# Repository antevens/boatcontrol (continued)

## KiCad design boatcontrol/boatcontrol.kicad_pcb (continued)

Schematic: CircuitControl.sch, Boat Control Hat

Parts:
D4101: 20mA R/G CC; LED_D5.0mm-3
SW4101, SW4102: ESB30; SW_PUSH_ESB30_DPDT

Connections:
+12P: SW4101.6 (C), SW4102.6 (C); also elsewhere on the board
/Add-On Relay Board 1/MixedBlock1/MixedControl1/DIG_OFF: SW4101.4 (A); also elsewhere on the board
/Add-On Relay Board 1/MixedBlock1/MixedControl1/DIG_ON: SW4102.4 (A); also elsewhere on the board
/Add-On Relay Board 1/MixedBlock1/MixedControl1/DISABLED_INDICATOR: SW4101.3 (C), SW4102.3 (C)
/Add-On Relay Board 1/MixedBlock1/MixedControl1/OFF_LED: D4101.3 (A2); also elsewhere on the board
/Add-On Relay Board 1/MixedBlock1/MixedControl1/OFF_TO_ON: SW4101.1 (A), SW4102.5 (B)
/Add-On Relay Board 1/MixedBlock1/MixedControl1/ON_LED: D4101.1 (A1); also elsewhere on the board
/Add-On Relay Board 1/MixedBlock1/MixedControl1/ON_TO_OFF: SW4101.5 (B), SW4102.1 (A)
/Add-On Relay Board 1/MixedBlock1/OFF_SIGNAL_1: SW4101.2 (B); also elsewhere on the board
/Add-On Relay Board 1/MixedBlock1/ON_SIGNAL_1: SW4102.2 (B); also elsewhere on the board
GND: D4101.2 (K); also elsewhere on the board

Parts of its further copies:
D4201, D4301, D4401, D4601, D4701, D4801, D4901, D8901, D9001, D9101, D9201, D9401, D9501, D9601, D9701: 20mA R/G CC; LED_D5.0mm-3
SW4201, SW4202, SW4301, SW4302, SW4401, SW4402, SW4601, SW4602, SW4701, SW4702, SW4801, SW4802, SW4901, SW4902, SW8901, SW8902, SW9001, SW9002, SW9101, SW9102, SW9201, SW9202, SW9401, SW9402, SW9501, SW9502, SW9601, SW9602, SW9701, SW9702: ESB30; SW_PUSH_ESB30_DPDT

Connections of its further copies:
+12P: SW4201.6 (C), SW4202.6 (C), SW4301.6 (C), SW4302.6 (C), SW4401.6 (C), SW4402.6 (C), SW4601.6 (C), SW4602.6 (C), SW4701.6 (C), SW4702.6 (C), SW4801.6 (C), SW4802.6 (C), SW4901.6 (C), SW4902.6 (C), SW8901.6 (C), SW8902.6 (C), SW9001.6 (C), SW9002.6 (C), SW9101.6 (C), SW9102.6 (C), SW9201.6 (C), SW9202.6 (C), SW9401.6 (C), SW9402.6 (C), SW9501.6 (C), SW9502.6 (C), SW9601.6 (C), SW9602.6 (C), SW9701.6 (C), SW9702.6 (C); also elsewhere on the board
/Add-On Relay Board 1/MixedBlock1/MixedControl2/DIG_OFF: SW4401.4 (A); also elsewhere on the board
/Add-On Relay Board 1/MixedBlock1/MixedControl2/DIG_ON: SW4402.4 (A); also elsewhere on the board
/Add-On Relay Board 1/MixedBlock1/MixedControl2/DISABLED_INDICATOR: SW4401.3 (C), SW4402.3 (C)
/Add-On Relay Board 1/MixedBlock1/MixedControl2/OFF_LED: D4401.3 (A2); also elsewhere on the board
/Add-On Relay Board 1/MixedBlock1/MixedControl2/OFF_TO_ON: SW4401.1 (A), SW4402.5 (B)
/Add-On Relay Board 1/MixedBlock1/MixedControl2/ON_LED: D4401.1 (A1); also elsewhere on the board
/Add-On Relay Board 1/MixedBlock1/MixedControl2/ON_TO_OFF: SW4401.5 (B), SW4402.1 (A)
/Add-On Relay Board 1/MixedBlock1/MixedControl3/DIG_OFF: SW4201.4 (A); also elsewhere on the board
/Add-On Relay Board 1/MixedBlock1/MixedControl3/DIG_ON: SW4202.4 (A); also elsewhere on the board
/Add-On Relay Board 1/MixedBlock1/MixedControl3/DISABLED_INDICATOR: SW4201.3 (C), SW4202.3 (C)
/Add-On Relay Board 1/MixedBlock1/MixedControl3/OFF_LED: D4201.3 (A2); also elsewhere on the board
/Add-On Relay Board 1/MixedBlock1/MixedControl3/OFF_TO_ON: SW4201.1 (A), SW4202.5 (B)
/Add-On Relay Board 1/MixedBlock1/MixedControl3/ON_LED: D4201.1 (A1); also elsewhere on the board
/Add-On Relay Board 1/MixedBlock1/MixedControl3/ON_TO_OFF: SW4201.5 (B), SW4202.1 (A)
/Add-On Relay Board 1/MixedBlock1/MixedControl4/DIG_OFF: SW4301.4 (A); also elsewhere on the board
/Add-On Relay Board 1/MixedBlock1/MixedControl4/DIG_ON: SW4302.4 (A); also elsewhere on the board
/Add-On Relay Board 1/MixedBlock1/MixedControl4/DISABLED_INDICATOR: SW4301.3 (C), SW4302.3 (C)
/Add-On Relay Board 1/MixedBlock1/MixedControl4/OFF_LED: D4301.3 (A2); also elsewhere on the board
/Add-On Relay Board 1/MixedBlock1/MixedControl4/OFF_TO_ON: SW4301.1 (A), SW4302.5 (B)
/Add-On Relay Board 1/MixedBlock1/MixedControl4/ON_LED: D4301.1 (A1); also elsewhere on the board
/Add-On Relay Board 1/MixedBlock1/MixedControl4/ON_TO_OFF: SW4301.5 (B), SW4302.1 (A)
/Add-On Relay Board 1/MixedBlock1/OFF_SIGNAL_2: SW4401.2 (B); also elsewhere on the board
/Add-On Relay Board 1/MixedBlock1/OFF_SIGNAL_3: SW4201.2 (B); also elsewhere on the board
/Add-On Relay Board 1/MixedBlock1/OFF_SIGNAL_4: SW4301.2 (B); also elsewhere on the board
/Add-On Relay Board 1/MixedBlock1/ON_SIGNAL_2: SW4402.2 (B); also elsewhere on the board
/Add-On Relay Board 1/MixedBlock1/ON_SIGNAL_3: SW4202.2 (B); also elsewhere on the board
/Add-On Relay Board 1/MixedBlock1/ON_SIGNAL_4: SW4302.2 (B); also elsewhere on the board
/Add-On Relay Board 1/MixedBlock2/MixedControl1/DIG_OFF: SW4601.4 (A); also elsewhere on the board
/Add-On Relay Board 1/MixedBlock2/MixedControl1/DIG_ON: SW4602.4 (A); also elsewhere on the board
/Add-On Relay Board 1/MixedBlock2/MixedControl1/DISABLED_INDICATOR: SW4601.3 (C), SW4602.3 (C)
/Add-On Relay Board 1/MixedBlock2/MixedControl1/OFF_LED: D4601.3 (A2); also elsewhere on the board
/Add-On Relay Board 1/MixedBlock2/MixedControl1/OFF_TO_ON: SW4601.1 (A), SW4602.5 (B)
/Add-On Relay Board 1/MixedBlock2/MixedControl1/ON_LED: D4601.1 (A1); also elsewhere on the board
/Add-On Relay Board 1/MixedBlock2/MixedControl1/ON_TO_OFF: SW4601.5 (B), SW4602.1 (A)
/Add-On Relay Board 1/MixedBlock2/MixedControl2/DIG_OFF: SW4901.4 (A); also elsewhere on the board
/Add-On Relay Board 1/MixedBlock2/MixedControl2/DIG_ON: SW4902.4 (A); also elsewhere on the board
/Add-On Relay Board 1/MixedBlock2/MixedControl2/DISABLED_INDICATOR: SW4901.3 (C), SW4902.3 (C)
/Add-On Relay Board 1/MixedBlock2/MixedControl2/OFF_LED: D4901.3 (A2); also elsewhere on the board
/Add-On Relay Board 1/MixedBlock2/MixedControl2/OFF_TO_ON: SW4901.1 (A), SW4902.5 (B)
/Add-On Relay Board 1/MixedBlock2/MixedControl2/ON_LED: D4901.1 (A1); also elsewhere on the board
/Add-On Relay Board 1/MixedBlock2/MixedControl2/ON_TO_OFF: SW4901.5 (B), SW4902.1 (A)
/Add-On Relay Board 1/MixedBlock2/MixedControl3/DIG_OFF: SW4701.4 (A); also elsewhere on the board
/Add-On Relay Board 1/MixedBlock2/MixedControl3/DIG_ON: SW4702.4 (A); also elsewhere on the board
/Add-On Relay Board 1/MixedBlock2/MixedControl3/DISABLED_INDICATOR: SW4701.3 (C), SW4702.3 (C)
/Add-On Relay Board 1/MixedBlock2/MixedControl3/OFF_LED: D4701.3 (A2); also elsewhere on the board
/Add-On Relay Board 1/MixedBlock2/MixedControl3/OFF_TO_ON: SW4701.1 (A), SW4702.5 (B)
/Add-On Relay Board 1/MixedBlock2/MixedControl3/ON_LED: D4701.1 (A1); also elsewhere on the board
/Add-On Relay Board 1/MixedBlock2/MixedControl3/ON_TO_OFF: SW4701.5 (B), SW4702.1 (A)
/Add-On Relay Board 1/MixedBlock2/MixedControl4/DIG_OFF: SW4801.4 (A); also elsewhere on the board
/Add-On Relay Board 1/MixedBlock2/MixedControl4/DIG_ON: SW4802.4 (A); also elsewhere on the board
/Add-On Relay Board 1/MixedBlock2/MixedControl4/DISABLED_INDICATOR: SW4801.3 (C), SW4802.3 (C)
/Add-On Relay Board 1/MixedBlock2/MixedControl4/OFF_LED: D4801.3 (A2); also elsewhere on the board
/Add-On Relay Board 1/MixedBlock2/MixedControl4/OFF_TO_ON: SW4801.1 (A), SW4802.5 (B)
/Add-On Relay Board 1/MixedBlock2/MixedControl4/ON_LED: D4801.1 (A1); also elsewhere on the board
/Add-On Relay Board 1/MixedBlock2/MixedControl4/ON_TO_OFF: SW4801.5 (B), SW4802.1 (A)
/Add-On Relay Board 1/MixedBlock2/OFF_SIGNAL_1: SW4601.2 (B); also elsewhere on the board
/Add-On Relay Board 1/MixedBlock2/OFF_SIGNAL_2: SW4901.2 (B); also elsewhere on the board
/Add-On Relay Board 1/MixedBlock2/OFF_SIGNAL_3: SW4701.2 (B); also elsewhere on the board
/Add-On Relay Board 1/MixedBlock2/OFF_SIGNAL_4: SW4801.2 (B); also elsewhere on the board
/Add-On Relay Board 1/MixedBlock2/ON_SIGNAL_1: SW4602.2 (B); also elsewhere on the board
/Add-On Relay Board 1/MixedBlock2/ON_SIGNAL_2: SW4902.2 (B); also elsewhere on the board
/Add-On Relay Board 1/MixedBlock2/ON_SIGNAL_3: SW4702.2 (B); also elsewhere on the board
/Add-On Relay Board 1/MixedBlock2/ON_SIGNAL_4: SW4802.2 (B); also elsewhere on the board
/Add-On Relay Board 2/MixedBlock1/MixedControl1/DIG_OFF: SW8902.4 (A); also elsewhere on the board
/Add-On Relay Board 2/MixedBlock1/MixedControl1/DIG_ON: SW8901.4 (A); also elsewhere on the board
/Add-On Relay Board 2/MixedBlock1/MixedControl1/DISABLED_INDICATOR: SW8901.3 (C), SW8902.3 (C)
/Add-On Relay Board 2/MixedBlock1/MixedControl1/OFF_LED: D8901.3 (A2); also elsewhere on the board
/Add-On Relay Board 2/MixedBlock1/MixedControl1/OFF_TO_ON: SW8901.5 (B), SW8902.1 (A)
/Add-On Relay Board 2/MixedBlock1/MixedControl1/ON_LED: D8901.1 (A1); also elsewhere on the board
/Add-On Relay Board 2/MixedBlock1/MixedControl1/ON_TO_OFF: SW8901.1 (A), SW8902.5 (B)
/Add-On Relay Board 2/MixedBlock1/MixedControl2/DIG_OFF: SW9202.4 (A); also elsewhere on the board
/Add-On Relay Board 2/MixedBlock1/MixedControl2/DIG_ON: SW9201.4 (A); also elsewhere on the board
/Add-On Relay Board 2/MixedBlock1/MixedControl2/DISABLED_INDICATOR: SW9201.3 (C), SW9202.3 (C)
/Add-On Relay Board 2/MixedBlock1/MixedControl2/OFF_LED: D9201.3 (A2); also elsewhere on the board
/Add-On Relay Board 2/MixedBlock1/MixedControl2/OFF_TO_ON: SW9201.5 (B), SW9202.1 (A)
/Add-On Relay Board 2/MixedBlock1/MixedControl2/ON_LED: D9201.1 (A1); also elsewhere on the board
/Add-On Relay Board 2/MixedBlock1/MixedControl2/ON_TO_OFF: SW9201.1 (A), SW9202.5 (B)
/Add-On Relay Board 2/MixedBlock1/MixedControl3/DIG_OFF: SW9002.4 (A); also elsewhere on the board
/Add-On Relay Board 2/MixedBlock1/MixedControl3/DIG_ON: SW9001.4 (A); also elsewhere on the board
/Add-On Relay Board 2/MixedBlock1/MixedControl3/DISABLED_INDICATOR: SW9001.3 (C), SW9002.3 (C)
/Add-On Relay Board 2/MixedBlock1/MixedControl3/OFF_LED: D9001.3 (A2); also elsewhere on the board
/Add-On Relay Board 2/MixedBlock1/MixedControl3/OFF_TO_ON: SW9001.5 (B), SW9002.1 (A)
/Add-On Relay Board 2/MixedBlock1/MixedControl3/ON_LED: D9001.1 (A1); also elsewhere on the board
/Add-On Relay Board 2/MixedBlock1/MixedControl3/ON_TO_OFF: SW9001.1 (A), SW9002.5 (B)
/Add-On Relay Board 2/MixedBlock1/MixedControl4/DIG_OFF: SW9102.4 (A); also elsewhere on the board
/Add-On Relay Board 2/MixedBlock1/MixedControl4/DIG_ON: SW9101.4 (A); also elsewhere on the board
/Add-On Relay Board 2/MixedBlock1/MixedControl4/DISABLED_INDICATOR: SW9101.3 (C), SW9102.3 (C)
/Add-On Relay Board 2/MixedBlock1/MixedControl4/OFF_LED: D9101.3 (A2); also elsewhere on the board
/Add-On Relay Board 2/MixedBlock1/MixedControl4/OFF_TO_ON: SW9101.5 (B), SW9102.1 (A)
/Add-On Relay Board 2/MixedBlock1/MixedControl4/ON_LED: D9101.1 (A1); also elsewhere on the board
/Add-On Relay Board 2/MixedBlock1/MixedControl4/ON_TO_OFF: SW9101.1 (A), SW9102.5 (B)
/Add-On Relay Board 2/MixedBlock1/OFF_SIGNAL_1: SW8902.2 (B); also elsewhere on the board
/Add-On Relay Board 2/MixedBlock1/OFF_SIGNAL_2: SW9202.2 (B); also elsewhere on the board
/Add-On Relay Board 2/MixedBlock1/OFF_SIGNAL_3: SW9002.2 (B); also elsewhere on the board
/Add-On Relay Board 2/MixedBlock1/OFF_SIGNAL_4: SW9102.2 (B); also elsewhere on the board
/Add-On Relay Board 2/MixedBlock1/ON_SIGNAL_1: SW8901.2 (B); also elsewhere on the board
/Add-On Relay Board 2/MixedBlock1/ON_SIGNAL_2: SW9201.2 (B); also elsewhere on the board
/Add-On Relay Board 2/MixedBlock1/ON_SIGNAL_3: SW9001.2 (B); also elsewhere on the board
/Add-On Relay Board 2/MixedBlock1/ON_SIGNAL_4: SW9101.2 (B); also elsewhere on the board
/Add-On Relay Board 2/MixedBlock2/MixedControl1/DIG_OFF: SW9402.4 (A); also elsewhere on the board
/Add-On Relay Board 2/MixedBlock2/MixedControl1/DIG_ON: SW9401.4 (A); also elsewhere on the board
/Add-On Relay Board 2/MixedBlock2/MixedControl1/DISABLED_INDICATOR: SW9401.3 (C), SW9402.3 (C)
/Add-On Relay Board 2/MixedBlock2/MixedControl1/OFF_LED: D9401.3 (A2); also elsewhere on the board
/Add-On Relay Board 2/MixedBlock2/MixedControl1/OFF_TO_ON: SW9401.5 (B), SW9402.1 (A)
/Add-On Relay Board 2/MixedBlock2/MixedControl1/ON_LED: D9401.1 (A1); also elsewhere on the board
/Add-On Relay Board 2/MixedBlock2/MixedControl1/ON_TO_OFF: SW9401.1 (A), SW9402.5 (B)
/Add-On Relay Board 2/MixedBlock2/MixedControl2/DIG_OFF: SW9702.4 (A); also elsewhere on the board
/Add-On Relay Board 2/MixedBlock2/MixedControl2/DIG_ON: SW9701.4 (A); also elsewhere on the board
/Add-On Relay Board 2/MixedBlock2/MixedControl2/DISABLED_INDICATOR: SW9701.3 (C), SW9702.3 (C)
/Add-On Relay Board 2/MixedBlock2/MixedControl2/OFF_LED: D9701.3 (A2); also elsewhere on the board
/Add-On Relay Board 2/MixedBlock2/MixedControl2/OFF_TO_ON: SW9701.5 (B), SW9702.1 (A)
/Add-On Relay Board 2/MixedBlock2/MixedControl2/ON_LED: D9701.1 (A1); also elsewhere on the board
/Add-On Relay Board 2/MixedBlock2/MixedControl2/ON_TO_OFF: SW9701.1 (A), SW9702.5 (B)
/Add-On Relay Board 2/MixedBlock2/MixedControl3/DIG_OFF: SW9502.4 (A); also elsewhere on the board
/Add-On Relay Board 2/MixedBlock2/MixedControl3/DIG_ON: SW9501.4 (A); also elsewhere on the board
/Add-On Relay Board 2/MixedBlock2/MixedControl3/DISABLED_INDICATOR: SW9501.3 (C), SW9502.3 (C)
/Add-On Relay Board 2/MixedBlock2/MixedControl3/OFF_LED: D9501.3 (A2); also elsewhere on the board
/Add-On Relay Board 2/MixedBlock2/MixedControl3/OFF_TO_ON: SW9501.5 (B), SW9502.1 (A)
/Add-On Relay Board 2/MixedBlock2/MixedControl3/ON_LED: D9501.1 (A1); also elsewhere on the board
/Add-On Relay Board 2/MixedBlock2/MixedControl3/ON_TO_OFF: SW9501.1 (A), SW9502.5 (B)
/Add-On Relay Board 2/MixedBlock2/MixedControl4/DIG_OFF: SW9602.4 (A); also elsewhere on the board
/Add-On Relay Board 2/MixedBlock2/MixedControl4/DIG_ON: SW9601.4 (A); also elsewhere on the board
/Add-On Relay Board 2/MixedBlock2/MixedControl4/DISABLED_INDICATOR: SW9601.3 (C), SW9602.3 (C)
/Add-On Relay Board 2/MixedBlock2/MixedControl4/OFF_LED: D9601.3 (A2); also elsewhere on the board
/Add-On Relay Board 2/MixedBlock2/MixedControl4/OFF_TO_ON: SW9601.5 (B), SW9602.1 (A)
/Add-On Relay Board 2/MixedBlock2/MixedControl4/ON_LED: D9601.1 (A1); also elsewhere on the board
/Add-On Relay Board 2/MixedBlock2/MixedControl4/ON_TO_OFF: SW9601.1 (A), SW9602.5 (B)
/Add-On Relay Board 2/MixedBlock2/OFF_SIGNAL_1: SW9402.2 (B); also elsewhere on the board
/Add-On Relay Board 2/MixedBlock2/OFF_SIGNAL_2: SW9702.2 (B); also elsewhere on the board
/Add-On Relay Board 2/MixedBlock2/OFF_SIGNAL_3: SW9502.2 (B); also elsewhere on the board
/Add-On Relay Board 2/MixedBlock2/OFF_SIGNAL_4: SW9602.2 (B); also elsewhere on the board
/Add-On Relay Board 2/MixedBlock2/ON_SIGNAL_1: SW9401.2 (B); also elsewhere on the board
/Add-On Relay Board 2/MixedBlock2/ON_SIGNAL_2: SW9701.2 (B); also elsewhere on the board
/Add-On Relay Board 2/MixedBlock2/ON_SIGNAL_3: SW9501.2 (B); also elsewhere on the board
/Add-On Relay Board 2/MixedBlock2/ON_SIGNAL_4: SW9601.2 (B); also elsewhere on the board
GND: D4201.2 (K), D4301.2 (K), D4401.2 (K), D4601.2 (K), D4701.2 (K), D4801.2 (K), D4901.2 (K), D8901.2 (K), D9001.2 (K), D9101.2 (K), D9201.2 (K), D9401.2 (K), D9501.2 (K), D9601.2 (K), D9701.2 (K); also elsewhere on the board

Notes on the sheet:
Buttons offer manual overide of relays using direct 12V. There is no timing/pulse circuit when operating the switches so care should be taken not to energise relay coils for more than a few seconds. Setting each coil to "on" will disable the opposing coil to prevent both coils from being energnized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

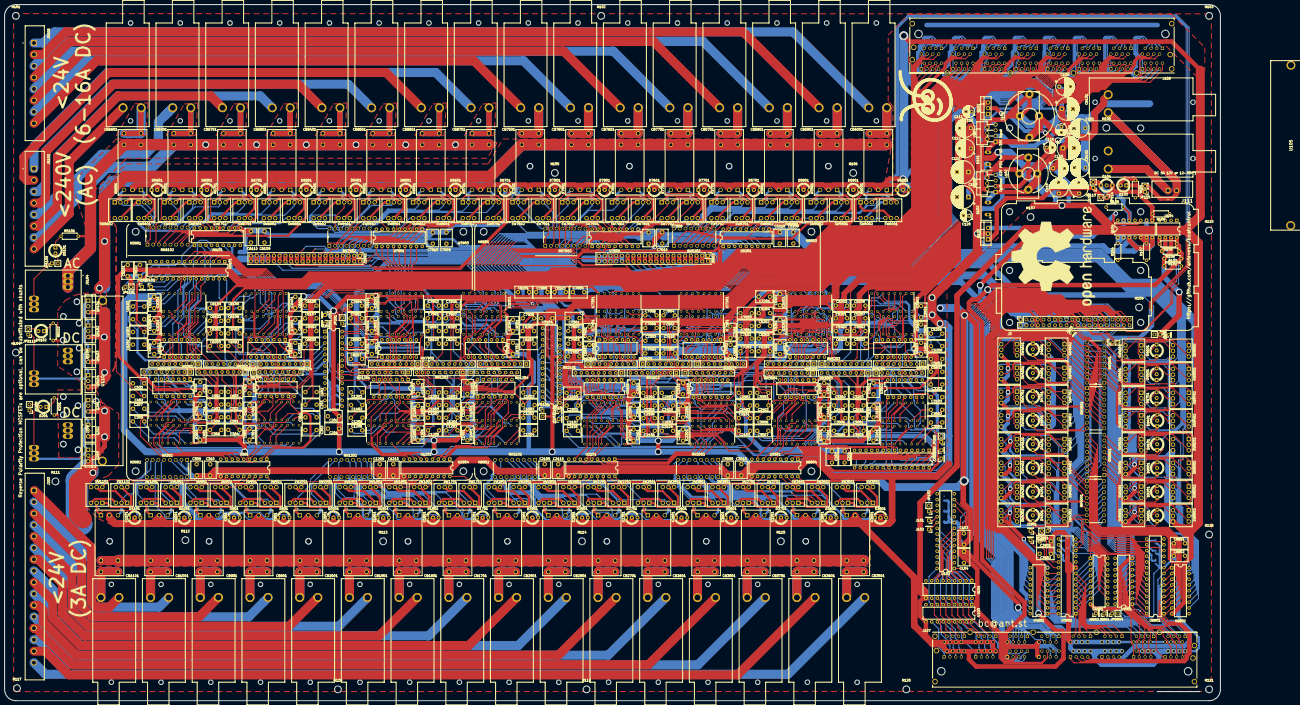
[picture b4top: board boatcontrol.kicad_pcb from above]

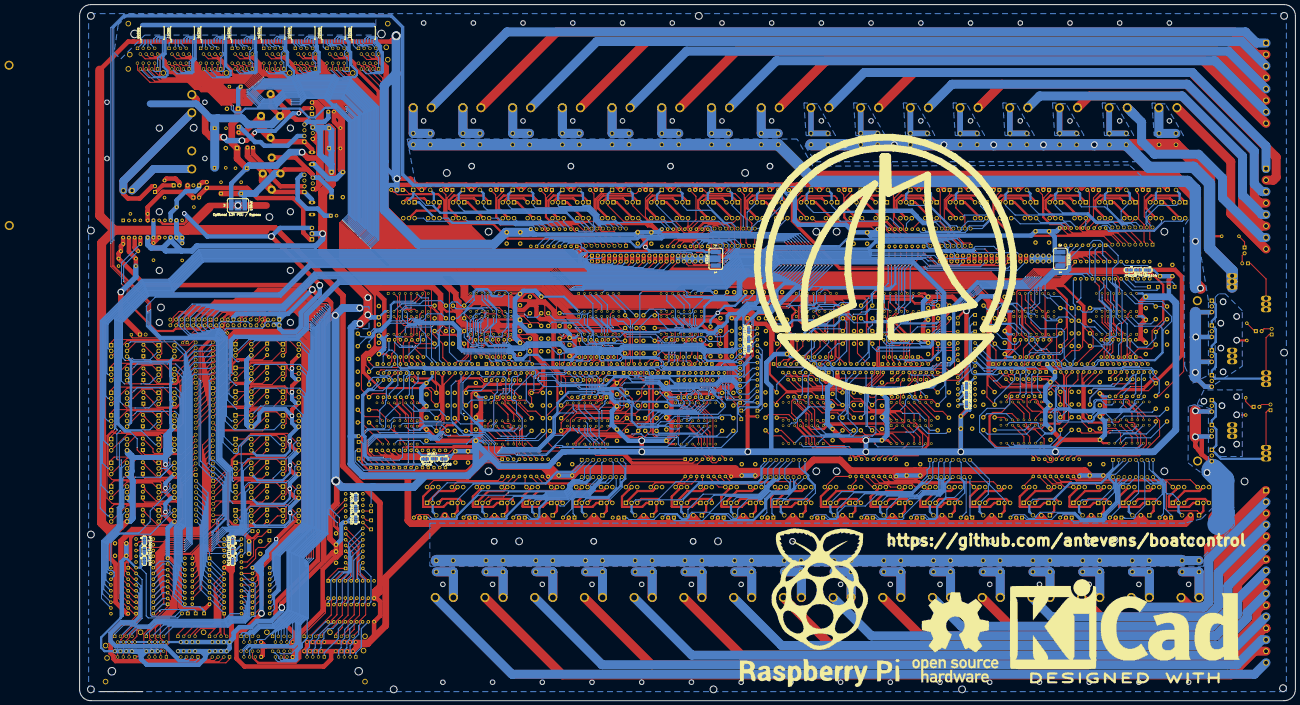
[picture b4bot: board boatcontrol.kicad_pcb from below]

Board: 2 copper layers, 538.0 x 308.0 mm, 683 parts (36 on the bottom side), 1183 nets.

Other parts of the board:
U105: OMNI-220-18-75-3C; OMNI22018753C

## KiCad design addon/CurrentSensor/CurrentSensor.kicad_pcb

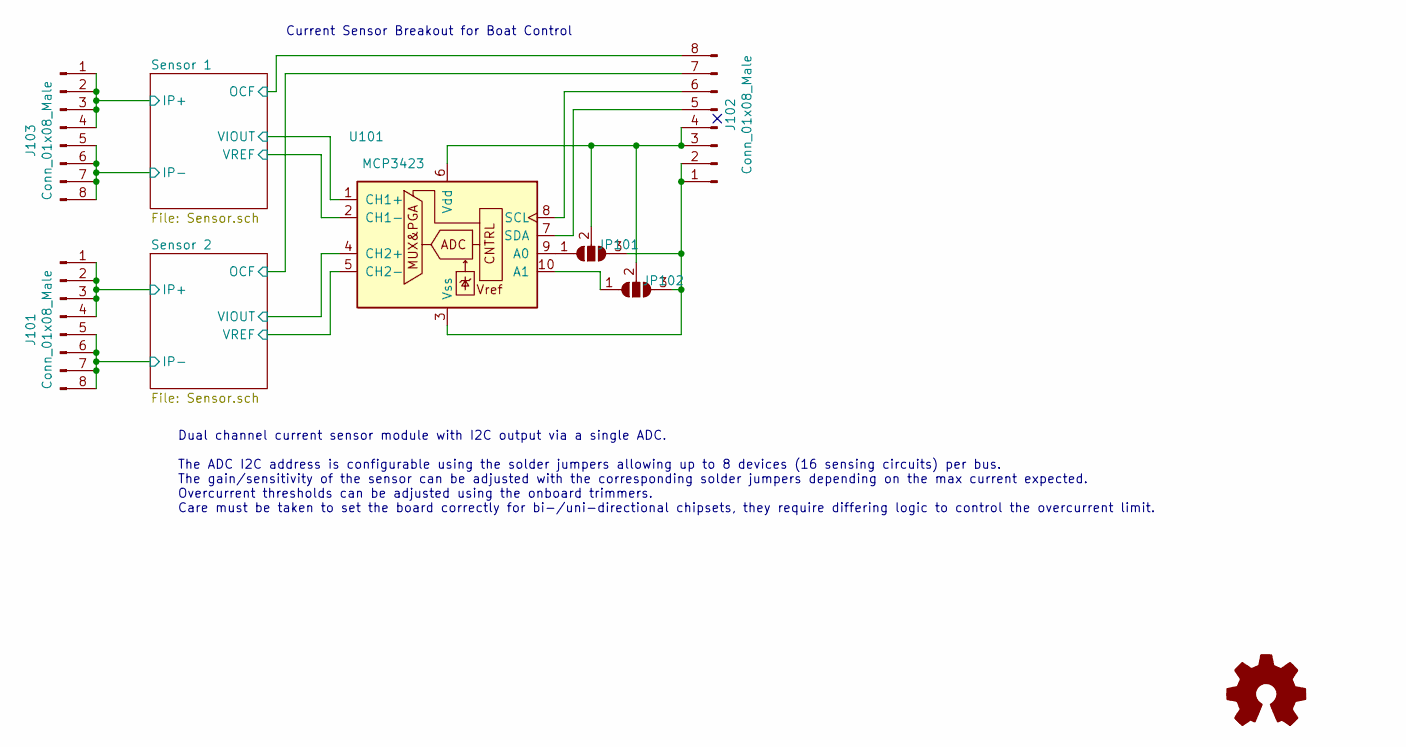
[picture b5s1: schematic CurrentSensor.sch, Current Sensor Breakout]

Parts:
J101, J102, J103: Conn_01x08_Male; PinHeader_1x08_P2.54mm_Vertical
JP101, JP102: SolderJumper_3_Open; SolderJumper-3_P1.3mm_Open_RoundedPad1.0x1.5mm
LOGO101: Logo_Open_Hardware_Small; OSHW-Logo2_7.3x6mm_SilkScreen
U101: MCP3423; MSOP-10_3x3mm_P0.5mm

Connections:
/Sensor 1/IP+: J103.1, J103.2, J103.3, J103.4; also elsewhere on the board
/Sensor 1/IP-: J103.5, J103.6, J103.7, J103.8; also elsewhere on the board
/Sensor 1/OCF: J102.8; also elsewhere on the board
/Sensor 1/VIOUT: U101.1 (CH1+); also elsewhere on the board
/Sensor 1/VREF: U101.2 (CH1-); also elsewhere on the board
/Sensor 2/IP+: J101.1, J101.2, J101.3, J101.4; also elsewhere on the board
/Sensor 2/IP-: J101.5, J101.6, J101.7, J101.8; also elsewhere on the board
/Sensor 2/OCF: J102.7; also elsewhere on the board
/Sensor 2/VIOUT: U101.4 (CH2+); also elsewhere on the board
/Sensor 2/VREF: U101.5 (CH2-); also elsewhere on the board
unnamed: J102.1, J102.2, JP101.3 (B), JP102.3 (B), U101.3 (Vss)
unnamed: J102.3, J102.4, JP101.2 (C), JP102.2 (C), U101.6 (Vdd)
unnamed: J102.5, U101.7 (SDA)
unnamed: J102.6, U101.8 (SCL)
unnamed: JP101.1 (A), U101.9 (A0)
unnamed: JP102.1 (A), U101.10 (A1)

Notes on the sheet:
Current Sensor Breakout for Boat Control
Dual channel current sensor module with I2C output via a single ADC. The ADC I2C address is configurable using the solder jumpers allowing up to 8 devices (16 sensing circuits) per bus. The gain/sensitivity of the sensor can be adjusted with the corresponding solder jumpers depending on the max cur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

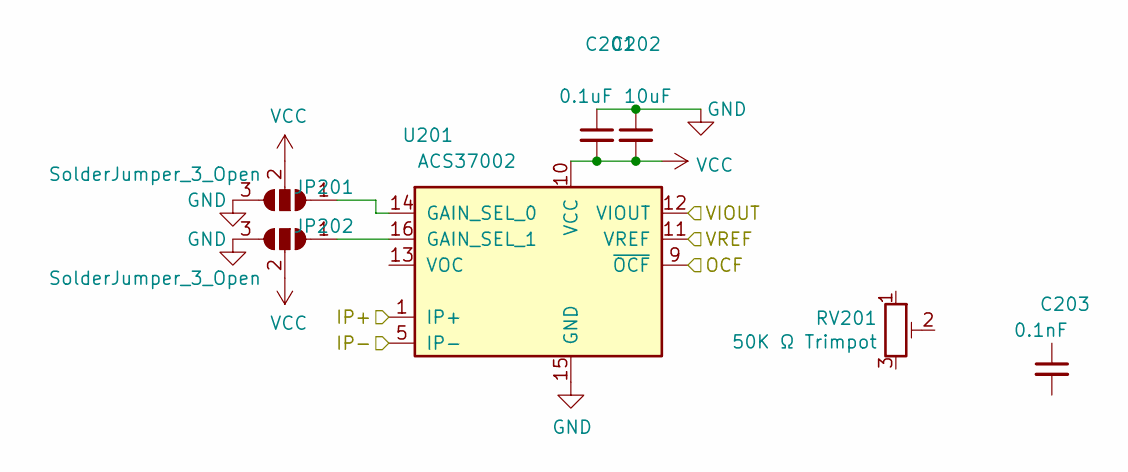
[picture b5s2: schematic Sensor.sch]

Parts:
C201: 0.1uF; C_1206_3216Metric_Pad1.33x1.80mm_HandSolder
C202: 10uF; C_1206_3216Metric_Pad1.33x1.80mm_HandSolder
C203: 0.1nF; C_1206_3216Metric_Pad1.33x1.80mm_HandSolder
JP201, JP202: SolderJumper_3_Open; SolderJumper-3_P1.3mm_Open_RoundedPad1.0x1.5mm
RV201: 50K Ω Trimpot; Potentiometer_Bourns_3214W_Vertical
U201: ACS37002; SOIC-16W_7.5x10.3mm_P1.27mm

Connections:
/Sensor 1/IP+: U201.1 (IP+), U201.2 (IP+), U201.3 (IP+), U201.4 (IP+); also elsewhere on the board
/Sensor 1/IP-: U201.5 (IP-), U201.6 (IP-), U201.7 (IP-), U201.8 (IP-); also elsewhere on the board
/Sensor 1/OCF: U201.9 (~OCF); also elsewhere on the board
/Sensor 1/VIOUT: U201.12 (VIOUT); also elsewhere on the board
/Sensor 1/VREF: U201.11 (VREF); also elsewhere on the board
GND: C201.1, C202.1, JP201.3 (B), JP202.3 (B), U201.15 (GND); also elsewhere on the board
unnamed: JP201.1 (A), U201.14 (GAIN_SEL_0)
unnamed: JP202.1 (A), U201.16 (GAIN_SEL_1)
VCC: C201.2, C202.2, JP201.2 (C), JP202.2 (C), U201.10 (VCC); also elsewhere on the board

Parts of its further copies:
C301: 0.1uF; C_1206_3216Metric_Pad1.33x1.80mm_HandSolder
C302: 10uF; C_1206_3216Metric_Pad1.33x1.80mm_HandSolder
C303: 0.1nF; C_1206_3216Metric_Pad1.33x1.80mm_HandSolder
JP301, JP302: SolderJumper_3_Open; SolderJumper-3_P1.3mm_Open_RoundedPad1.0x1.5mm
RV301: 50K Ω Trimpot; Potentiometer_Bourns_3214W_Vertical
U301: ACS37002; SOIC-16W_7.5x10.3mm_P1.27mm

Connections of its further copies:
/Sensor 2/IP+: U301.1 (IP+), U301.2 (IP+), U301.3 (IP+), U301.4 (IP+); also elsewhere on the board
/Sensor 2/IP-: U301.5 (IP-), U301.6 (IP-), U301.7 (IP-), U301.8 (IP-); also elsewhere on the board
/Sensor 2/OCF: U301.9 (~OCF); also elsewhere on the board
/Sensor 2/VIOUT: U301.12 (VIOUT); also elsewhere on the board
/Sensor 2/VREF: U301.11 (VREF); also elsewhere on the board
GND: C301.1, C302.1, JP301.3 (B), JP302.3 (B), U301.15 (GND); also elsewhere on the board
unnamed: JP301.1 (A), U301.14 (GAIN_SEL_0)
unnamed: JP302.1 (A), U301.16 (GAIN_SEL_1)
VCC: C301.2, C302.2, JP301.2 (C), JP302.2 (C), U301.10 (VCC); also elsewhere on the board

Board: 2 copper layers, 21 parts (3 on the bottom side), 22 nets, no tracks yet.

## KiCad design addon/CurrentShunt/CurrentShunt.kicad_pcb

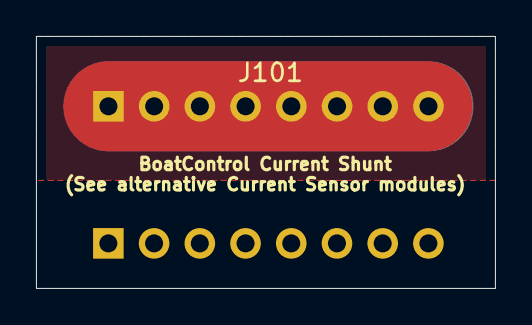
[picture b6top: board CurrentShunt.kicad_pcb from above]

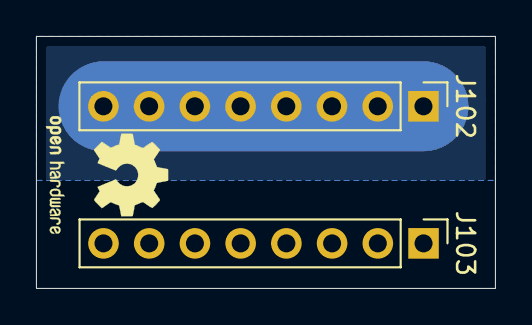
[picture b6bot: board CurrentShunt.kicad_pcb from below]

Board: 2 copper layers, 25.5 x 14.0 mm, 4 parts (3 on the bottom side), 9 nets.

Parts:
J101: Current Bridge; DIP-16_W7.62mm
J102, J103: Conn_01x08_Male; PinHeader_1x08_P2.54mm_Vertical
LOGO101: Logo_Open_Hardware_Small; OSHW-Logo2_7.3x6mm_SilkScreen

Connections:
/Power: J101.9, J101.10, J101.11, J101.12, J101.13, J101.14, J101.15, J101.16, J103.1, J103.2, J103.3, J103.4, J103.5, J103.6, J103.7, J103.8
unnamed: J101.1, J102.1
unnamed: J101.2, J102.2
unnamed: J101.3, J102.3
unnamed: J101.4, J102.4
unnamed: J101.5, J102.5
unnamed: J101.6, J102.6
unnamed: J101.7, J102.7
unnamed: J101.8, J102.8

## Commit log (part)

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2020-12-24 replistep2
2020-12-28 More cleanup
2020-12-28 Defina add-on boards
2020-12-29 Split add-ons
2020-12-29 Fix second addon board
2020-12-29 Fix mad hatter
2020-12-29 Add mad hatter
2020-12-29 Big hat fix
2020-12-29 RPi scheme update done
2020-12-29 Fixed RPi Footprint
2020-12-29 vibrator cleanup and layout
2020-12-29 mil cleanup
2020-12-29 Fix addon outlines
2020-12-29 Fix resistor network values
2020-12-29 Multi
2020-12-29 Left Sorted
2020-12-30 Fix cap
2020-12-30 Text cleanup
2020-12-30 Copy/paste
2020-12-30 Rewiring resistors done
2020-12-30 SecondBlock
2020-12-30 FixBugs
2020-12-30 Interal routing for multivibrators done
2020-12-30 Line up jumpers
2020-12-30 Put solder jumpers in place
2020-12-30 Add Node-RED flows
2020-12-30 Prettify json
2020-12-30 More Work
2020-12-30 First vias
2020-12-30 Power
2020-12-30 Undo
2020-12-30 Wire again
2020-12-31 Lineup
2020-12-31 Fix mosfet
2020-12-31 Fix power traces
2020-12-31 Let's wire this
2020-12-31 New deal
2020-12-31 Better
2021-01-02 Fix SB footprint and symbol
2021-01-03 Scale reverse polarity protection
2021-01-03 Second CB
2021-01-04 Boxes
2021-01-04 Cleaner
2021-01-04 Add notes about power use of polarity protection
2021-01-04 Add warnings and options
2021-01-04 Cleanup
2021-01-05 Add Current Shunt
2021-01-05 Add Current Sensor
2021-01-05 Add missing files
2021-01-05 Fix power interconnects
2021-01-05 Park Current Sensing
2021-01-05 Add more fets, you can never have enough fets
2021-01-05 Update description
2021-01-05 Fix power fills to fets
2021-01-06 Second bank
2021-01-06 More wiring
2021-01-06 Upper switches
2021-01-06 mwire
2021-01-06 Route vibrators
2021-01-06 Add heatsinks
2021-01-07 Move centre right
2021-01-07 moved
2021-01-08 Fits
2021-01-08 Fix 3d models
2021-01-08 Fix silkscreen logos and graphics
2021-01-08 Re-wire channel
2021-01-09 Power work
2021-01-11 Add signal diodes
2021-01-11 Re-label
2021-01-11 Moved Diodes
2021-01-11 Time to rewire centre
2021-01-11 No tracks
2021-01-11 alligned
2021-01-11 Before multi tool
2021-01-11 Protowire
2021-01-11 Upper
2021-01-11 Second set
2021-01-11 Working on it
2021-01-13 Green
2021-01-14 shuffle
2021-01-14 Newcluster
2021-01-14 organized
2021-01-14 greener
2021-01-14 Nice
2021-01-14 more
2021-01-14 cross
2021-01-14 It fits
2021-01-14 progress
2021-01-14 step
2021-01-14 Too many circuits
2021-01-17 Add git ignore
2021-01-17 Fix missing symbols
2021-01-18 Fix rescued symbols
2021-01-22 Fix more rescue stuff
2021-01-25 Cleanup schematic
2021-02-14 Add xors on input
2021-02-14 add second e-section
2021-02-15 Renamed
2021-02-15 Update cap numbering
2021-02-15 Clean re-wiring centre
2021-02-15 Switch to common 5v 10K ohm for an sigs
2021-02-16 Better 60a board
2021-02-16 Fix green
2021-02-16 Less ugly
2021-02-16 Better still
2021-02-16 Add text to silkscreen
2021-02-16 Add caps for xors
2021-02-16 Sorted Caps
2021-02-17 Lined up
2021-02-17 compacted
2021-02-17 Wows
2021-02-17 It fits!
2021-02-17 Rollback to re-order
2021-02-17 Re-ordered
2021-02-17 Good fit
2021-02-17 I give up, SMD resistors for RJ45
2021-02-24 NewPattern before split
2021-02-24 In alligment
2021-02-24 Clustersomethnig
2021-02-24 Not bad
2021-02-24 Start alignment
2021-02-27 Alligning
2021-02-27 Nicely ordered
2021-02-27 It kind of fits
2021-02-28 Next steps
2021-03-01 keepouts
2021-03-01 Fix right
2021-03-02 Add Nvidia Jetson stuff
2021-03-02 Niceties
2021-03-03 stuff
2021-03-03 Hacks and bodges
2021-03-03 Ugly is as ugly does
2021-03-03 Bunch of fracking bullpoop
2021-03-03 Add logos
2021-03-04 Wiring wiring wiring
2021-03-05 Right side mostly done
2021-03-05 Tired, fairly tired
2021-03-05 Move caps
2021-03-09 Fix upper routing
2021-03-11 Let's fix this
2021-03-11 Better org
2021-03-13 Make it bigger
2021-03-13 Move cap cluster
2021-03-13 Rewiring
2021-03-13 again and again and again
2021-03-15 Git powers
2021-03-18 MoveCaps
2021-03-18 Routed
2021-03-18 Nice Fills
2021-03-18 I guess I removed the heat sink
2021-03-18 Big swap
2021-03-18 Small fix
2021-03-19 Cleanup silkscreen
2021-03-19 Step 1
2021-03-19 Step 2
2021-03-19 Step 3
2021-03-19 Step 4
2021-03-19 Step 5
2021-03-19 Done
2021-03-19 Bugfixing
2021-03-19 Bugfixes without update
2021-03-19 Rework 6702
2021-03-19 Wohoo
2021-03-19 Clean tracks
2021-03-19 Stepping stone
2021-03-22 Let's do this
2021-03-22 Before swap
2021-03-22 Good swap
2021-03-22 Probably OK
2021-03-22 Easy
2021-03-23 Start over
2021-03-23 Going
2021-03-24 Wired
2021-03-24 Upper done
2021-03-25 Done and done
2021-03-25 Hackawackatacka
2021-03-31 Stepping stones
2021-03-31 Shift
2021-03-31 b4pack
2021-03-31 Around we go
2021-03-31 Center hashing
2021-03-31 work work work, all I do is work :P
2021-04-01 bit by bit
2021-04-01 Fix silly vias
2021-04-01 Step step .. stepper motor ?
2021-04-01 break
2021-04-02 Without power
2021-04-02 Rest
2021-04-02 sort sort
2021-04-02 Reroute 5v south
2021-04-03 Wired
    Only power and I2C left
    (also debugging and fills)
2021-04-03 Resize
2021-04-03 Deleting second heatsink
2021-04-03 Better decals
2021-04-03 Power is back
2021-04-03 Grounded
2021-04-04 Bugs, fixes bugs, bugspray
2021-04-04 Dimples
2021-04-04 Two left
2021-04-04 I2C done
2021-04-05 Let's start debugging
2021-04-05 More ground down
2021-04-05 Connected
2021-04-05 Via spacing .. and more spacing
2021-04-05 Let's go 4 layers
2021-04-06 Adapting to 4 layers
2021-04-06 Fix zone clearances
2021-04-06 Let's fix spacing for power
2021-04-06 Reconnected
2021-04-06 D .. deee, deebuggging
2021-04-06 Re-introduce second heatsink
2021-04-06 Reworking zones
2021-04-06 Better fills
2021-04-06 Error Free
2021-04-06 Fix silkscreen
2021-04-06 Full of bugs, I just don't know about them
2021-04-07 Vias for solderjumpers, silkscreen, minor routing
2021-04-07 Added poetry
2021-04-08 Silkscreen text and minor adjustments
2021-04-08 Fix images
2021-04-08 Fix 60 Relay board
2021-04-08 Placing relays on 30A addon board
2021-04-08 Need to trim down 30A addon board traces to 2.7
2021-04-08 Fix readme
2021-04-08 Fix up silkscreen and numbering
2021-04-09 Done?
2021-04-09 Final fixes before revision 6
    Fixes to size, dimensions add Revision and hash to board
2021-04-09 Revision 6
2021-04-09 Refs on board
2021-04-09 Production Output Generated
2021-04-09 Final for 60A Addon Board
2021-04-09 Add git refs for 60A addon board
2021-04-09 Wrap up non-latching
2021-04-09 Revision 2 of non-latching
2021-04-09 Prototype time
2021-04-09 More plotting
2021-04-09 Update readme and 3d models for addon-boards
2021-04-10 Minor stuff, perfection is the enemy of good enough
2021-04-10 Text, manufacturinqg details, silkscreen
2021-04-11 Fix spelling and text
2021-04-11 Update docs
2021-04-11 Fix docs
2021-04-11 Add enclosure
2021-04-11 Better images, text, etc
2021-04-11 Add DigiKey and Mouser part numbers to symbols
2021-04-11 Fix RPi/Jetson footprint
2021-04-11 Fix circuit breaker symbol
2021-04-12 Probably a dead end, this stuff is borked
2021-04-12 Add node-red screenshots
2021-04-12 Fix wording
2021-04-12 Stop hotlinking gpio pinout
2021-04-12 Fix spelling mistake
2021-04-12 Revision 7
2021-04-12 Update onboard git ref
2021-04-12 Fix spelling and typos
2021-04-12 Add renderings of addon boards
2021-04-12 More reading
2021-04-12 Update branch link for 2layers
2021-04-12 Fix url for 2layer
2021-04-12 That's annoying
2021-04-12 Headless ants
2021-04-12 It's common.. not common ground
2021-04-14 Minor cleanup and fixes
2021-04-16 Fix thermal reliefs for solder pads
2021-04-19 Via spacing issues
2021-04-19 Fix second batch of via spacing
2021-04-19 More via clearance
2021-04-20 I hate my life
2021-04-20 Possibly resolved all via issues
2021-04-20 Bad ideas and worse implementations
2021-04-20 I'm just a software person
2021-04-20 grog
2021-04-20 more and more and more
2021-04-20 Fix the fixes for a fix
2021-04-20 Fixed via spacing
2021-04-20 Revision 8
2021-04-20 Rev8 release
2021-04-21 Let's try kicad 6
2021-04-23 Morph to buried vias and remove pad vias
2021-04-23 Cleanup for production
2021-04-23 Revision 9
2021-04-23 Add git ref
2021-04-23 Revision 10
2021-04-23 Spit and polish
2021-04-26 Fix readme for ESD protection
2021-04-26 Fix thermal relief for bottom connector
2021-04-26 Fix some pours and paths
2021-04-26 Add nota about panelization
2021-05-04 Start changes
2021-05-04 Fix production issues
2021-05-05 Revision 11
2021-05-05 Bump ref and revision
2021-05-07 Update board data
2021-05-09 Fix 12v line on bottom for clearance
2021-05-20 Minor polish
2021-05-20 Fix pour outlines
2021-05-23 Small fixes to pours and two vias
2021-05-23 Clean up tracks north of addon switches
2021-05-25 Fix spelling
2021-07-17 Add power consumption for bare board
2021-07-18 Update images
2021-07-18 Remove mention of discontinued Moitessier HAT
2021-07-19 Add hat submodule
2021-07-19 Add EPROM skeleton
2021-07-27 Update Node-Red config
2021-07-31 Add BoatControl Logo
2021-08-02 Update node-red for night/day skins
2021-08-03 Add note about NMEA/Seatalk and hats
2021-08-04 Update node-red
2021-08-05 Update node-red code for mobile, add evo-home code
2021-08-05 Add Boatcontrol logo for Node-Red
2021-08-06 Update Node-red configuration and setup
2021-08-06 Add disable delays to node-red
2021-08-08 Update Readme on power consumption
2021-08-08 Small wording updates
2021-08-08 Update screenshots and add dark image
2022-04-19 Mostly done with logic
2022-04-19 Break up ports for easier routing
2022-04-19 Intermediate
2022-04-20 Looking Good
2022-04-24 Fix Bel Fuse polyfuses
2022-04-25 Added more polyfuses
2022-04-25 Rough draft
2022-04-25 Outline
2022-04-25 Phase1
2022-04-25 Top done
2022-04-25 Topper
2022-04-25 Right side
2022-04-25 Swirls
2022-04-26 Steps
2022-04-27 Patcha patcha
2022-04-28 Via whatever
2022-04-28 Short stubs
2022-04-29 steps steps steps
2022-04-29 bottom
2022-04-29 details, details details
2022-04-29 More down
2022-04-29 Rework
2022-04-30 making things
2022-05-01 Left done
2022-05-02 Inter
2022-05-02 Morish
2022-05-03 Fixer upper
2022-05-03 More fixes
2022-05-03 Fix power rails
2022-05-04 Power and Ground
2022-05-22 Improvements
2022-06-21 Switch to SMD caps
2022-06-22 New position for caps
2022-06-22 Tracked
2022-06-22 Flip caps and fix bugs
2022-06-22 Fixed simple areas
2022-06-22 Need to fix courtyards
2022-06-22 Fixed layers for caps
2022-06-22 Half way there
2022-06-22 No errors
2022-06-22 Fix a couple of bugs
2022-06-22 Fixing and fixing
2022-06-22 Meshed
2022-06-22 Fixin to fix
2022-06-22 Switch breakout 0.1
2022-06-23 SwitchBreakout 0.1
